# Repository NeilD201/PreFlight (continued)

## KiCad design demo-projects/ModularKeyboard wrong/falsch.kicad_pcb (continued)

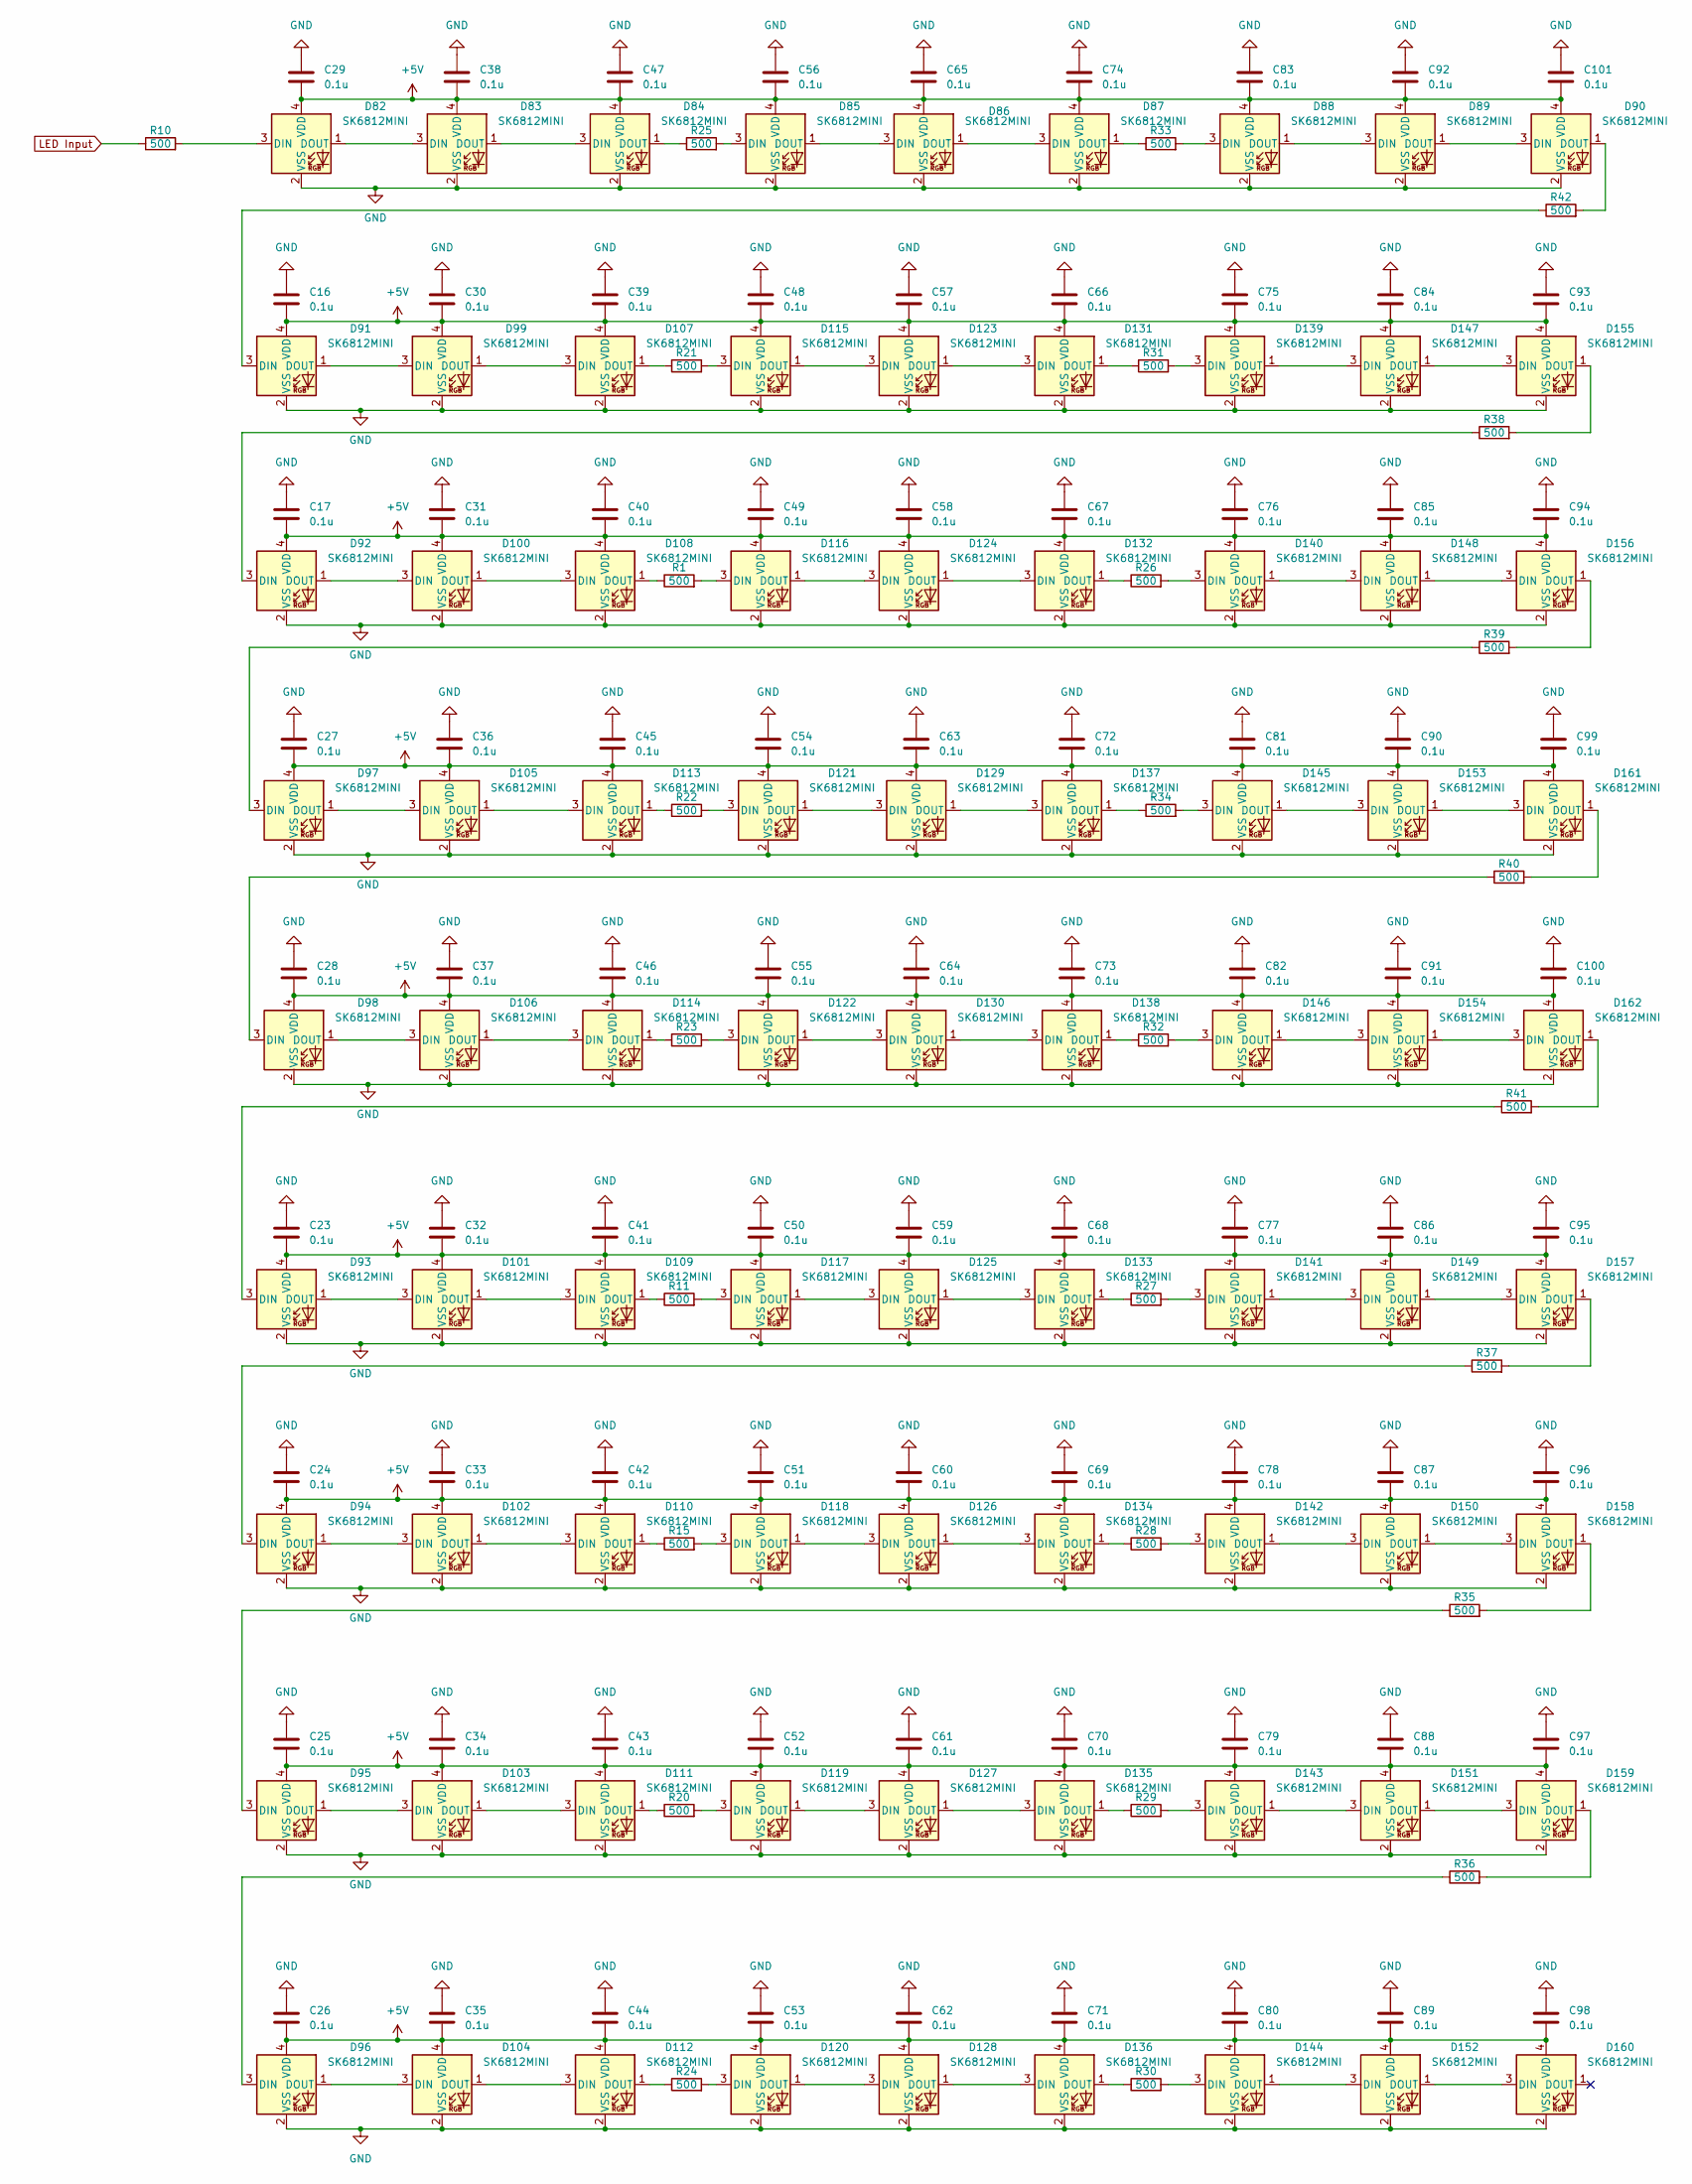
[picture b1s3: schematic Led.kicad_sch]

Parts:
C16, C17, C23, C24, C25, C26, C27, C28, C29, C30, C31, C32, C33, C34, C35, C36, C37, C38, C39, C40, C41, C42, C43, C44, C45, C46, C47, C48, C49, C50, C51, C52, C53, C54, C55, C56, C57, C58, C59, C60, C61, C62, C63, C64, C65, C66, C67, C68, C69, C70, C71, C72, C73, C74, C75, C76, C77, C78, C79, C80, C81, C82, C83, C84, C85, C86, C87, C88, C89, C90, C91, C92, C93, C94, C95, C96, C97, C98, C99, C100, C101: 0.1u; C_0402_1005Metric
D82, D83, D84, D85, D86, D87, D88, D89, D90, D91, D92, D93, D94, D95, D96, D97, D98, D99, D100, D101, D102, D103, D104, D105, D106, D107, D108, D109, D110, D111, D112, D113, D114, D115, D116, D117, D118, D119, D120, D121, D122, D123, D124, D125, D126, D127, D128, D129, D130, D131, D132, D133, D134, D135, D136, D137, D138, D139, D140, D141, D142, D143, D144, D145, D146, D147, D148, D149, D150, D151, D152, D153, D154, D155, D156, D157, D158, D159, D160, D161, D162: SK6812MINI; SK6812MINI-012 (Updated3)
R1, R10, R11, R15, R20, R21, R22, R23, R24, R25, R26, R27, R28, R29, R30, R31, R32, R33, R34, R35, R36, R37, R38, R39, R40, R41, R42: 500; R_0402_1005Metric

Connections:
+5V: C16.2, C17.2, C23.2, C24.2, C25.2, C26.2, C27.2, C28.2, C29.2, C30.2, C31.2, C32.2, C33.2, C34.2, C35.2, C36.2, C37.2, C38.2, C39.2, C40.2, C41.2, C42.2, C43.2, C44.2, C45.2, C46.2, C47.2, C48.2, C49.2, C50.2, C51.2, C52.2, C53.2, C54.2, C55.2, C56.2, C57.2, C58.2, C59.2, C60.2, C61.2, C62.2, C63.2, C64.2, C65.2, C66.2, C67.2, C68.2, C69.2, C70.2, C71.2, C72.2, C73.2, C74.2, C75.2, C76.2, C77.2, C78.2, C79.2, C80.2, C81.2, C82.2, C83.2, C84.2, C85.2, C86.2, C87.2, C88.2, C89.2, C90.2, C91.2, C92.2, C93.2, C94.2, C95.2, C96.2, C97.2, C98.2, C99.2, C100.2, C101.2, D82.4 (VDD), D83.4 (VDD), D84.4 (VDD), D85.4 (VDD), D86.4 (VDD), D87.4 (VDD), D88.4 (VDD), D89.4 (VDD), D90.4 (VDD), D91.4 (VDD), D92.4 (VDD), D93.4 (VDD), D94.4 (VDD), D95.4 (VDD), D96.4 (VDD), D97.4 (VDD), D98.4 (VDD), D99.4 (VDD), D100.4 (VDD), D101.4 (VDD), D102.4 (VDD), D103.4 (VDD), D104.4 (VDD), D105.4 (VDD), D106.4 (VDD), D107.4 (VDD), D108.4 (VDD), D109.4 (VDD), D110.4 (VDD), D111.4 (VDD), D112.4 (VDD), D113.4 (VDD), D114.4 (VDD), D115.4 (VDD), D116.4 (VDD), D117.4 (VDD), D118.4 (VDD), D119.4 (VDD), D120.4 (VDD), D121.4 (VDD), D122.4 (VDD), D123.4 (VDD), D124.4 (VDD), D125.4 (VDD), D126.4 (VDD), D127.4 (VDD), D128.4 (VDD), D129.4 (VDD), D130.4 (VDD), D131.4 (VDD), D132.4 (VDD), D133.4 (VDD), D134.4 (VDD), D135.4 (VDD), D136.4 (VDD), D137.4 (VDD), D138.4 (VDD), D139.4 (VDD), D140.4 (VDD), D141.4 (VDD), D142.4 (VDD), D143.4 (VDD), D144.4 (VDD), D145.4 (VDD), D146.4 (VDD), D147.4 (VDD), D148.4 (VDD), D149.4 (VDD), D150.4 (VDD), D151.4 (VDD), D152.4 (VDD), D153.4 (VDD), D154.4 (VDD), D155.4 (VDD), D156.4 (VDD), D157.4 (VDD), D158.4 (VDD), D159.4 (VDD), D160.4 (VDD), D161.4 (VDD), D162.4 (VDD); also elsewhere on the board
GND: C16.1, C17.1, C23.1, C24.1, C25.1, C26.1, C27.1, C28.1, C29.1, C30.1, C31.1, C32.1, C33.1, C34.1, C35.1, C36.1, C37.1, C38.1, C39.1, C40.1, C41.1, C42.1, C43.1, C44.1, C45.1, C46.1, C47.1, C48.1, C49.1, C50.1, C51.1, C52.1, C53.1, C54.1, C55.1, C56.1, C57.1, C58.1, C59.1, C60.1, C61.1, C62.1, C63.1, C64.1, C65.1, C66.1, C67.1, C68.1, C69.1, C70.1, C71.1, C72.1, C73.1, C74.1, C75.1, C76.1, C77.1, C78.1, C79.1, C80.1, C81.1, C82.1, C83.1, C84.1, C85.1, C86.1, C87.1, C88.1, C89.1, C90.1, C91.1, C92.1, C93.1, C94.1, C95.1, C96.1, C97.1, C98.1, C99.1, C100.1, C101.1, D82.2 (VSS), D83.2 (VSS), D84.2 (VSS), D85.2 (VSS), D86.2 (VSS), D87.2 (VSS), D88.2 (VSS), D89.2 (VSS), D90.2 (VSS), D91.2 (VSS), D92.2 (VSS), D93.2 (VSS), D94.2 (VSS), D95.2 (VSS), D96.2 (VSS), D97.2 (VSS), D98.2 (VSS), D99.2 (VSS), D100.2 (VSS), D101.2 (VSS), D102.2 (VSS), D103.2 (VSS), D104.2 (VSS), D105.2 (VSS), D106.2 (VSS), D107.2 (VSS), D108.2 (VSS), D109.2 (VSS), D110.2 (VSS), D111.2 (VSS), D112.2 (VSS), D113.2 (VSS), D114.2 (VSS), D115.2 (VSS), D116.2 (VSS), D117.2 (VSS), D118.2 (VSS), D119.2 (VSS), D120.2 (VSS), D121.2 (VSS), D122.2 (VSS), D123.2 (VSS), D124.2 (VSS), D125.2 (VSS), D126.2 (VSS), D127.2 (VSS), D128.2 (VSS), D129.2 (VSS), D130.2 (VSS), D131.2 (VSS), D132.2 (VSS), D133.2 (VSS), D134.2 (VSS), D135.2 (VSS), D136.2 (VSS), D137.2 (VSS), D138.2 (VSS), D139.2 (VSS), D140.2 (VSS), D141.2 (VSS), D142.2 (VSS), D143.2 (VSS), D144.2 (VSS), D145.2 (VSS), D146.2 (VSS), D147.2 (VSS), D148.2 (VSS), D149.2 (VSS), D150.2 (VSS), D151.2 (VSS), D152.2 (VSS), D153.2 (VSS), D154.2 (VSS), D155.2 (VSS), D156.2 (VSS), D157.2 (VSS), D158.2 (VSS), D159.2 (VSS), D160.2 (VSS), D161.2 (VSS), D162.2 (VSS); also elsewhere on the board
LED Input: R10.1; also elsewhere on the board
unnamed: D82.3 (DIN), R10.2
unnamed: D82.1 (DOUT), D83.3 (DIN)
unnamed: D83.1 (DOUT), D84.3 (DIN)
unnamed: D84.1 (DOUT), R25.1
unnamed: D85.3 (DIN), R25.2
unnamed: D85.1 (DOUT), D86.3 (DIN)
unnamed: D86.1 (DOUT), D87.3 (DIN)
unnamed: D87.1 (DOUT), R33.1
unnamed: D88.3 (DIN), R33.2
unnamed: D88.1 (DOUT), D89.3 (DIN)
unnamed: D89.1 (DOUT), D90.3 (DIN)
unnamed: D90.1 (DOUT), R42.2
unnamed: D91.3 (DIN), R42.1
unnamed: D91.1 (DOUT), D99.3 (DIN)
unnamed: D92.3 (DIN), R38.1
unnamed: D93.3 (DIN), R41.1
unnamed: D94.3 (DIN), R37.1
unnamed: D95.3 (DIN), R35.1
unnamed: D96.3 (DIN), R36.1
unnamed: D97.3 (DIN), R39.1
unnamed: D98.3 (DIN), R40.1
unnamed: D92.1 (DOUT), D100.3 (DIN)
unnamed: D100.1 (DOUT), D108.3 (DIN)
unnamed: D93.1 (DOUT), D101.3 (DIN)
unnamed: D101.1 (DOUT), D109.3 (DIN)
unnamed: D94.1 (DOUT), D102.3 (DIN)
unnamed: D102.1 (DOUT), D110.3 (DIN)
unnamed: D95.1 (DOUT), D103.3 (DIN)
unnamed: D103.1 (DOUT), D111.3 (DIN)
unnamed: D96.1 (DOUT), D104.3 (DIN)
unnamed: D104.1 (DOUT), D112.3 (DIN)
unnamed: D97.1 (DOUT), D105.3 (DIN)
unnamed: D105.1 (DOUT), D113.3 (DIN)
unnamed: D98.1 (DOUT), D106.3 (DIN)
unnamed: D106.1 (DOUT), D114.3 (DIN)
unnamed: D99.1 (DOUT), D107.3 (DIN)
unnamed: D107.1 (DOUT), R21.1
unnamed: D108.1 (DOUT), R1.1
unnamed: D109.1 (DOUT), R11.1
unnamed: D110.1 (DOUT), R15.1
unnamed: D111.1 (DOUT), R20.1
unnamed: D112.1 (DOUT), R24.1
unnamed: D113.1 (DOUT), R22.1
unnamed: D114.1 (DOUT), R23.1
unnamed: D115.3 (DIN), R21.2
unnamed: D115.1 (DOUT), D123.3 (DIN)
unnamed: D116.3 (DIN), R1.2
unnamed: D116.1 (DOUT), D124.3 (DIN)
unnamed: D117.3 (DIN), R11.2
unnamed: D117.1 (DOUT), D125.3 (DIN)
unnamed: D118.3 (DIN), R15.2
unnamed: D118.1 (DOUT), D126.3 (DIN)
unnamed: D119.3 (DIN), R20.2
unnamed: D119.1 (DOUT), D127.3 (DIN)
unnamed: D120.3 (DIN), R24.2
unnamed: D120.1 (DOUT), D128.3 (DIN)
unnamed: D121.3 (DIN), R22.2
unnamed: D121.1 (DOUT), D129.3 (DIN)
unnamed: D122.3 (DIN), R23.2
unnamed: D122.1 (DOUT), D130.3 (DIN)
unnamed: D123.1 (DOUT), D131.3 (DIN)
unnamed: D124.1 (DOUT), D132.3 (DIN)
unnamed: D125.1 (DOUT), D133.3 (DIN)
unnamed: D126.1 (DOUT), D134.3 (DIN)
unnamed: D127.1 (DOUT), D135.3 (DIN)
unnamed: D128.1 (DOUT), D136.3 (DIN)
unnamed: D129.1 (DOUT), D137.3 (DIN)
unnamed: D130.1 (DOUT), D138.3 (DIN)
unnamed: D131.1 (DOUT), R31.1
unnamed: D132.1 (DOUT), R26.1
unnamed: D133.1 (DOUT), R27.1
unnamed: D134.1 (DOUT), R28.1
unnamed: D135.1 (DOUT), R29.1
unnamed: D136.1 (DOUT), R30.1
unnamed: D137.1 (DOUT), R34.1
unnamed: D138.1 (DOUT), R32.1
unnamed: D139.3 (DIN), R31.2
unnamed: D139.1 (DOUT), D147.3 (DIN)
unnamed: D140.3 (DIN), R26.2
unnamed: D140.1 (DOUT), D148.3 (DIN)
unnamed: D141.3 (DIN), R27.2
unnamed: D141.1 (DOUT), D149.3 (DIN)
unnamed: D142.3 (DIN), R28.2
unnamed: D142.1 (DOUT), D150.3 (DIN)
unnamed: D143.3 (DIN), R29.2
unnamed: D143.1 (DOUT), D151.3 (DIN)
unnamed: D144.3 (DIN), R30.2
unnamed: D144.1 (DOUT), D152.3 (DIN)
unnamed: D145.3 (DIN), R34.2
unnamed: D145.1 (DOUT), D153.3 (DIN)
unnamed: D146.3 (DIN), R32.2
unnamed: D146.1 (DOUT), D154.3 (DIN)
unnamed: D147.1 (DOUT), D155.3 (DIN)
unnamed: D148.1 (DOUT), D156.3 (DIN)
unnamed: D149.1 (DOUT), D157.3 (DIN)
unnamed: D150.1 (DOUT), D158.3 (DIN)
unnamed: D151.1 (DOUT), D159.3 (DIN)
unnamed: D152.1 (DOUT), D160.3 (DIN)
unnamed: D153.1 (DOUT), D161.3 (DIN)
unnamed: D154.1 (DOUT), D162.3 (DIN)
unnamed: D155.1 (DOUT), R38.2
unnamed: D156.1 (DOUT), R39.2
unnamed: D157.1 (DOUT), R37.2
unnamed: D158.1 (DOUT), R35.2
unnamed: D159.1 (DOUT), R36.2
unnamed: D161.1 (DOUT), R40.2
unnamed: D162.1 (DOUT), R41.2

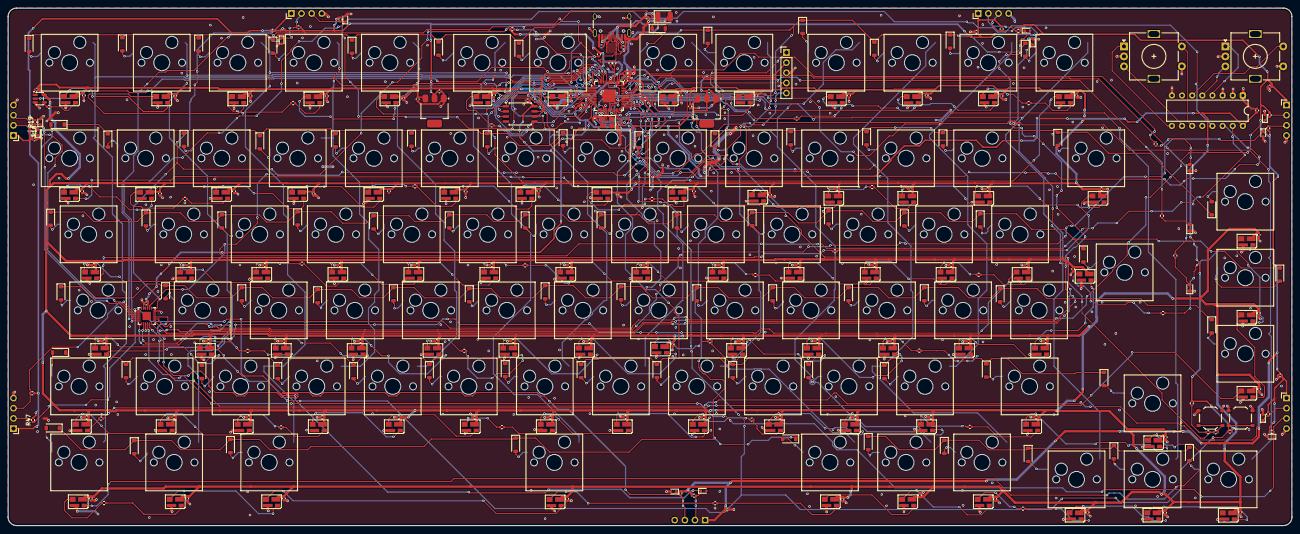
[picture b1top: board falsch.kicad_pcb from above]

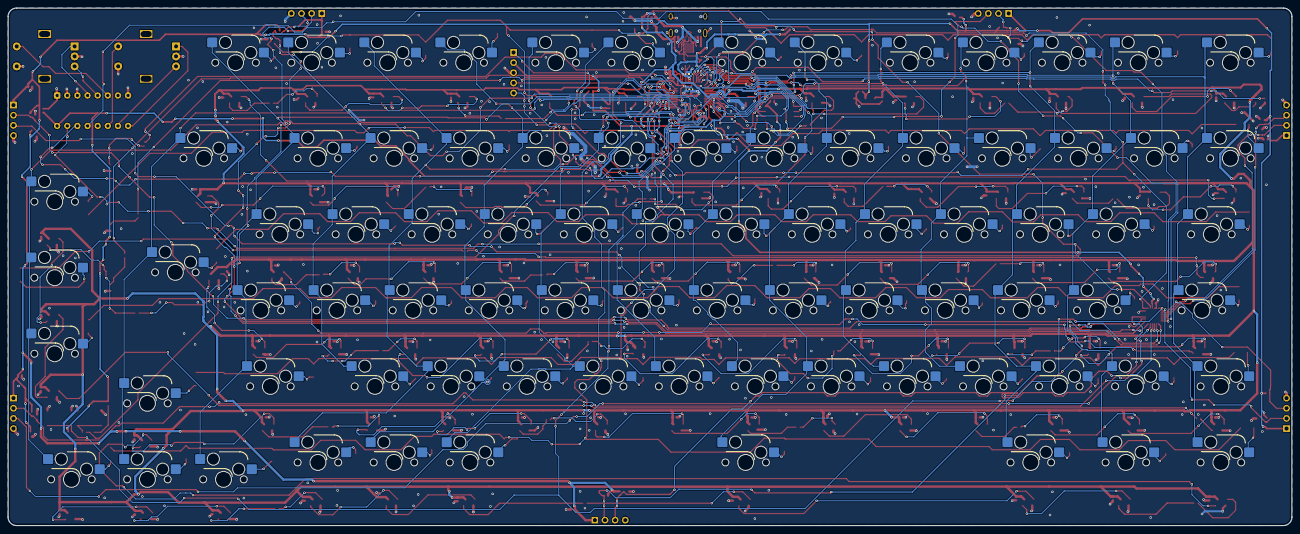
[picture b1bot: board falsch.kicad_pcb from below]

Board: 2 copper layers, 321.6 x 129.6 mm, 445 parts (5 on the bottom side), 265 nets.
